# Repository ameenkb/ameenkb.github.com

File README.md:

# Ameen. K. B
PAGE FOR FABLAB COURSE PROGRESS

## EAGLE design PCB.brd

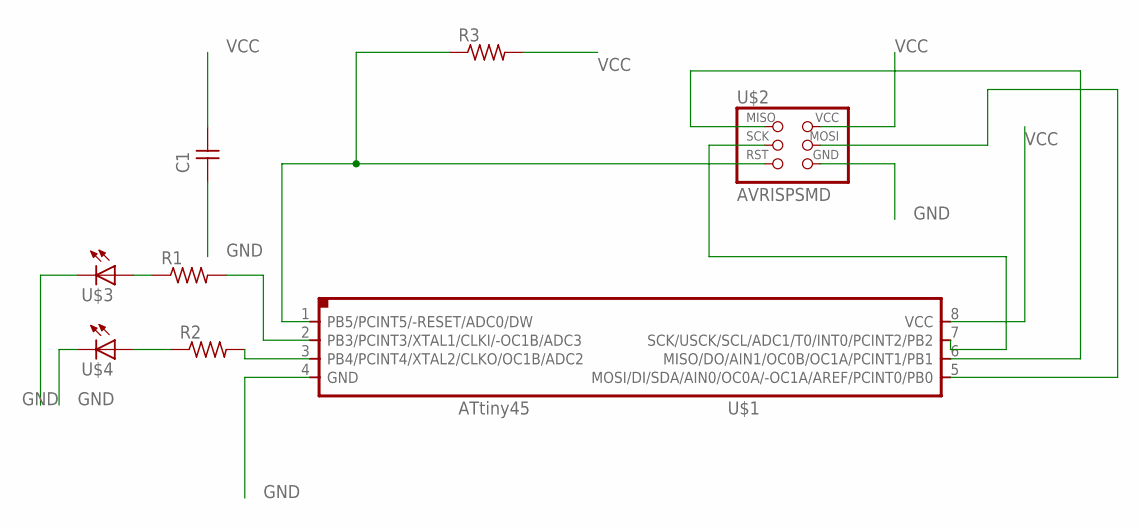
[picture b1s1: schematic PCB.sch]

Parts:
C1: UNPOLARIZED_CAPACITOR1206; 1206
R1, R2, R3: RESISTOR1206; 1206
U$1: ATTINY45SI; SOIC8
U$2: AVRISPSMD; 2X03SMD
U$3, U$4: LED1206; 1206

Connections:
GND: C1.1, U$1.4 (GND), U$2.6 (GND), U$3.2 (C), U$4.2 (C)
unnamed: R1.1, U$3.1 (A)
unnamed: R2.1, U$4.1 (A)
unnamed: U$1.7 (SCK/USCK/SCL/ADC1/T0/INT0/PCINT2/PB2), U$2.3 (SCK)
unnamed: R3.1, U$1.1 (PB5/PCINT5/-RESET/ADC0/DW), U$2.5 (RST)
unnamed: U$1.6 (MISO/DO/AIN1/OC0B/OC1A/PCINT1/PB1), U$2.1 (MISO)
unnamed: U$1.5 (MOSI/DI/SDA/AIN0/OC0A/-OC1A/AREF/PCINT0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), U$2.4 (MOSI)
unnamed: R1.2, U$1.2 (PB3/PCINT3/XTAL1/CLKI/-OC1B/ADC3)
unnamed: R2.2, U$1.3 (PB4/PCINT4/XTAL2/CLKO/OC1B/ADC2)
VCC: C1.2, R3.2, U$1.8 (VCC), U$2.2 (VCC)

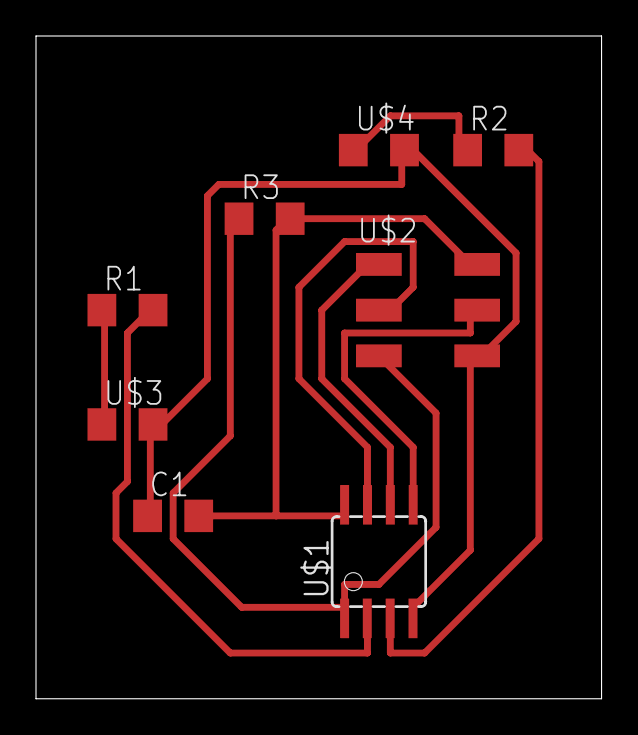
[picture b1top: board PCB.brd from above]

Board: 2 copper layers, 31.4 x 36.8 mm, 8 parts (0 on the bottom side), 10 nets.

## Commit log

2017-08-03 Set theme jekyll-theme-minimal
2017-08-03 Set theme jekyll-theme-modernist
2017-08-05 Set theme jekyll-theme-cayman
2017-08-06 Create 1
